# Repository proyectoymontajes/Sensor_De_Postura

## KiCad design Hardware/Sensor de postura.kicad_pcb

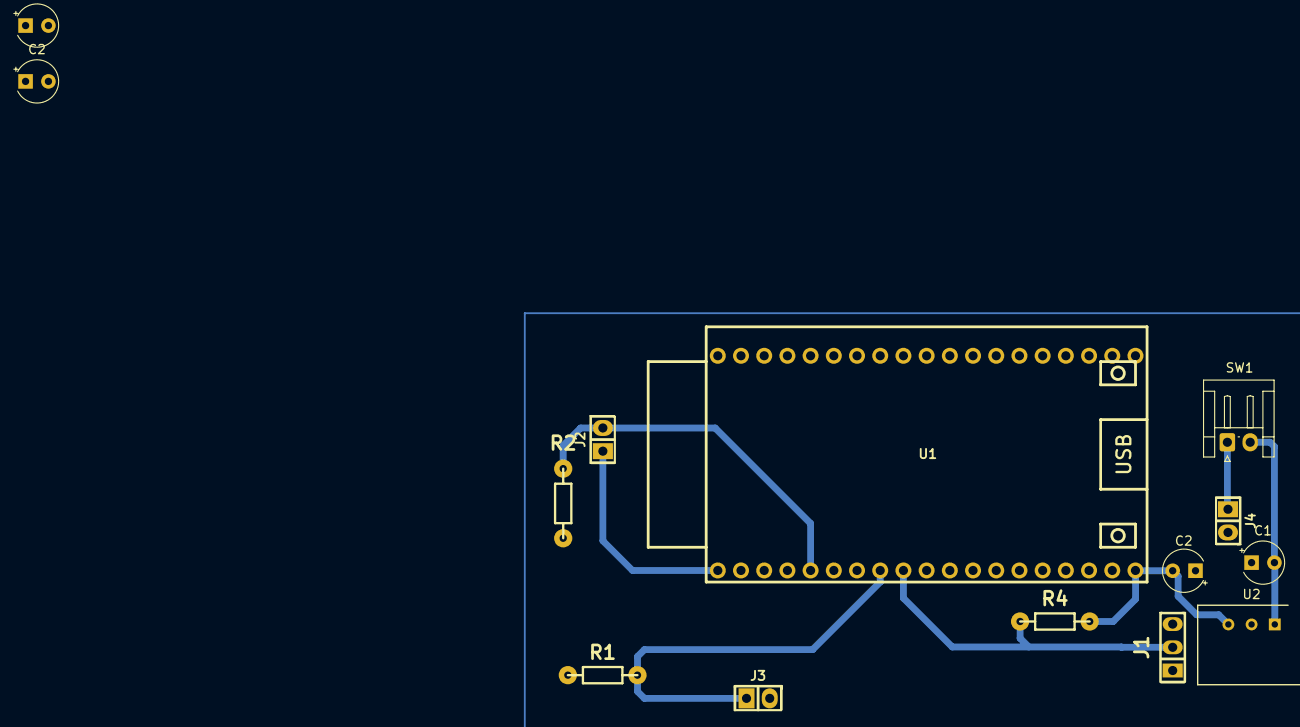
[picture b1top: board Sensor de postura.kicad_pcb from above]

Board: 2 copper layers, 14 parts (0 on the bottom side), 8 nets.

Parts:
C1, C1#2, C2, C2#2: 100nF; CP_Radial_Tantal_D4.5mm_P2.50mm
J1: Screw_Terminal_01x03; Pin_Header_3
J2, J4: Screw_Terminal_01x02; Pin_Header_2
J3: Pin_Header_2
R1: 200; RES0.3
R2: 10k; RES0.3
R4: 2k; RES0.3
SW1: SW_Omron_B3FS; JST_EH_S2B-EH_1x02_P2.50mm_Horizontal
U1: ESP32_DEVKITC
U2: L7805; SIP3_11.6x8.5mm

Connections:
/3V: J2.1, U1.1 (3V3)
/5V: C2.2, C2#2.2, R4.2, U1.19 (5V), U2.3 (OUT)
/Temp: J1.2, R4.1, U1.6 (IO35)
/incli: J2.2, R2.1, U1.5 (IO34)
/vibra: J3.1, R1.2, U1.8 (IO33)
GND: C1.1, C1#2.1, C2.1, C2#2.1, J1.1, J3.2, J4.2, R1.1, R2.2, U1.38 (GND), U2.2 (GND)
unnamed: J4.1, SW1.1
VCC: C1.2, C1#2.2, SW1.2, U2.1 (IN)
